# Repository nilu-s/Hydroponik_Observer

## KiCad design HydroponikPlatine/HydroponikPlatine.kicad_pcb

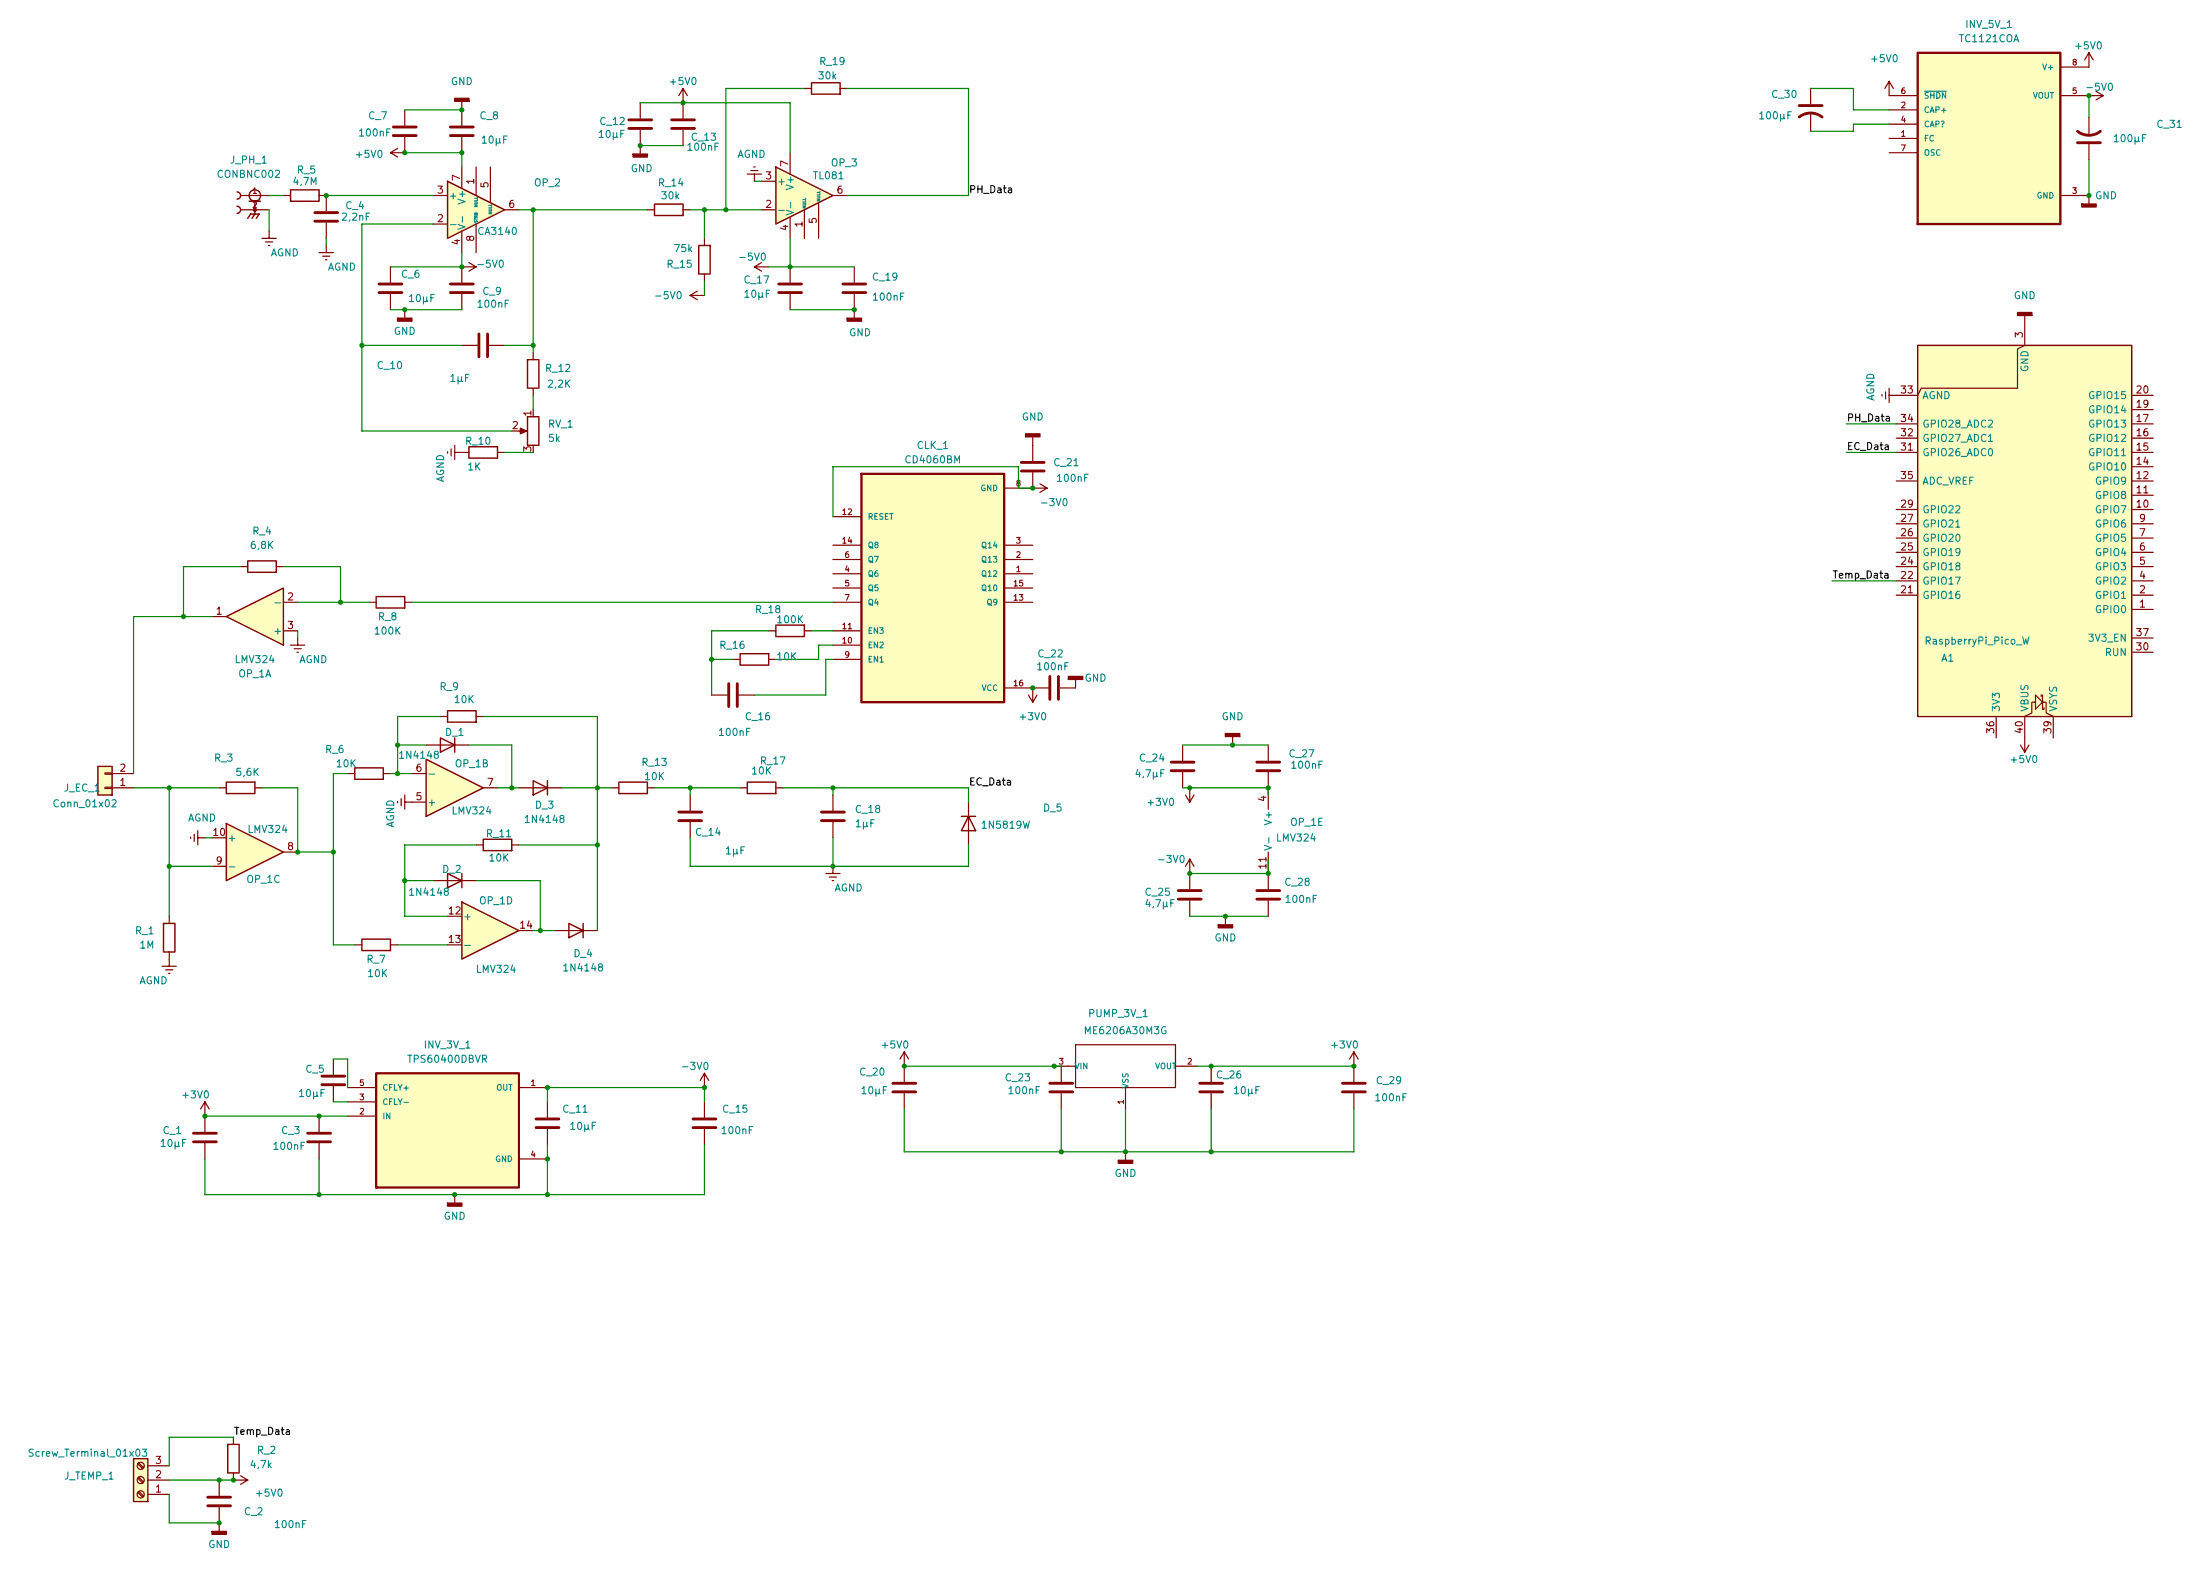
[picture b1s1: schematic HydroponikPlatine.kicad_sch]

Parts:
A1: RaspberryPi_Pico_W; RaspberryPi_Pico_Common_THT
CLK_1: CD4060BM; SOIC127P600X175-16N; LCSC C555139
C_1, C_5, C_6, C_8, C_11, C_12, C_17, C_20, C_26: 10µF; C_0201_0603Metric; LCSC C1691
C_2, C_3, C_7, C_9, C_13, C_15, C_16, C_19, C_21, C_22, C_23, C_27, C_28, C_29: 100nF; C_0402_1005Metric; LCSC C1525
C_4: 2,2nF; C_0201_0603Metric; LCSC C1531
C_10, C_14, C_18: 1µF; C_0201_0603Metric; LCSC C1592
C_24, C_25: 4,7µF; C_0201_0603Metric; LCSC C1705
C_30, C_31: 100µF; CAPPM6032X280N; LCSC C7222
D_1, D_2, D_3, D_4: 1N4148; D_SOD-123; LCSC C2099
D_5: 1N5819W; D_SOD-123F; LCSC C169540
INV_3V_1: TPS60400DBVR; SOT95P280X145-5N; LCSC C9839
INV_5V_1: TC1121COA; SOIC127P599X175-8N; LCSC C27529401
J_EC_1: Conn_01x02; JST_B2B-XH-A; LCSC C158012
J_PH_1: CONBNC002; LINX_CONBNC002; LCSC C22442694
J_TEMP_1: Screw_Terminal_01x03; TE_282834-3; LCSC C5172753
OP_1: LMV324; SOIC127P600X175-14N; LCSC C7974
OP_2: CA3140; SOIC127P602X173-8N; LCSC C5157700
OP_3: TL081; SOIC127P599X175-8N; LCSC C6965
PUMP_3V_1: ME6206A30M3G; SOT-23; MPN XC6206P332MR-G; LCSC C487911
RV_1: 5k; TRIM_3314J-1-502E; LCSC C58391
R_1: 1M; R_1206_3216Metric; LCSC C17927
R_2: 4,7k; R_0805_2012Metric; LCSC C17673
R_3: 5,6K; R_0805_2012Metric; LCSC C4382
R_4: 6,8K; R_0805_2012Metric; LCSC C17772
R_5: 4,7M; R_0402_1005Metric; LCSC C11906
R_6, R_7, R_9, R_11, R_13, R_16, R_17: 10K; R_1206_3216Metric; LCSC C1489
R_8, R_18: 100K; R_0603_1608Metric; LCSC C14675
R_10: 1K; R_1206_3216Metric; LCSC C1469
R_12: 2,2K; R_0603_1608Metric; LCSC C4190
R_14, R_19: 30k; R_0603_1608Metric; LCSC C18681
R_15: 75k; R_0805_2012Metric; LCSC C17819

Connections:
+3V0: CLK_1.16 (VCC), C_1.1, C_3.1, C_22.1, C_24.2, C_26.1, C_27.2, C_29.1, INV_3V_1.2 (IN), OP_1.4 (V+), PUMP_3V_1.2 (VOUT)
+5V0: A1.40 (VBUS), C_2.1, C_7.2, C_8.2, C_12.1, C_13.1, C_20.1, C_23.1, INV_5V_1.6 (~SHDN), INV_5V_1.8 (V+), J_TEMP_1.2, OP_2.7 (V+), OP_3.7 (V+), PUMP_3V_1.3 (VIN), R_2.1
-3V0: CLK_1.8 (GND), CLK_1.12 (RESET), C_11.1, C_15.1, C_21.1, C_25.2, C_28.2, INV_3V_1.1 (OUT), OP_1.11 (V-)
-5V0: C_6.1, C_9.1, C_17.1, C_19.1, C_31.2, INV_5V_1.5 (VOUT), OP_2.4 (V-), OP_3.4 (V-), R_15.1
/EC_Data: A1.31 (GPIO26_ADC0), C_18.1, D_5.1 (K), R_17.2
/PH_Data: A1.34 (GPIO28_ADC2), OP_3.6, R_19.2
/Temp_Data: A1.22 (GPIO17), J_TEMP_1.3, R_2.2
AGND: A1.33 (AGND), C_4.2, C_14.2, C_18.2, D_5.2 (A), J_PH_1.2, J_PH_1.S1, J_PH_1.S2, OP_1.3 (+), OP_1.5 (+), OP_1.10 (+), OP_3.3 (+), R_1.1, R_10.1
GND: A1.3 (GND), A1.8 (GND), A1.13 (GND), A1.18 (GND), A1.23 (GND), A1.28 (GND), A1.38 (GND), C_1.2, C_2.2, C_3.2, C_6.2, C_7.1, C_8.1, C_9.2, C_11.2, C_12.2, C_13.2, C_15.2, C_17.2, C_19.2, C_20.2, C_21.2, C_22.2, C_23.2, C_24.1, C_25.1, C_26.2, C_27.1, C_28.1, C_29.2, C_31.1, INV_3V_1.4 (GND), INV_5V_1.3 (GND), J_TEMP_1.1, PUMP_3V_1.1 (VSS)
unnamed: CLK_1.9 (EN1), C_16.2
unnamed: CLK_1.10 (EN2), R_16.2
unnamed: CLK_1.11 (EN3), R_18.2
unnamed: CLK_1.7 (Q4), R_8.2
unnamed: C_10.2, OP_2.6, R_12.2, R_14.1
unnamed: C_14.1, R_13.2, R_17.1
unnamed: C_16.1, R_16.1, R_18.1
unnamed: D_1.2 (A), OP_1.6 (-), R_6.2, R_9.1
unnamed: D_1.1 (K), D_3.2 (A), OP_1.7
unnamed: D_2.2 (A), OP_1.12 (+), R_11.1
unnamed: D_2.1 (K), D_4.2 (A), OP_1.14
unnamed: D_3.1 (K), D_4.1 (K), R_9.2, R_11.2, R_13.1
unnamed: C_5.1, INV_3V_1.5 (CFLY+)
unnamed: C_5.2, INV_3V_1.3 (CFLY-)
unnamed: C_30.1, INV_5V_1.2 (CAP+)
unnamed: C_30.2, INV_5V_1.4 (CAP?)
unnamed: J_EC_1.1, OP_1.9 (-), R_1.2, R_3.1
unnamed: J_EC_1.2, OP_1.1, R_4.1
unnamed: J_PH_1.1, R_5.1
unnamed: OP_1.8, R_3.2, R_6.1, R_7.1
unnamed: OP_1.2 (-), R_4.2, R_8.1
unnamed: OP_1.13 (-), R_7.2
unnamed: C_4.1, OP_2.3 (+), R_5.2
unnamed: C_10.1, OP_2.2 (-), RV_1.2
unnamed: OP_3.2 (-), R_14.2, R_15.2, R_19.1
unnamed: RV_1.1, R_12.1
unnamed: RV_1.3, R_10.2

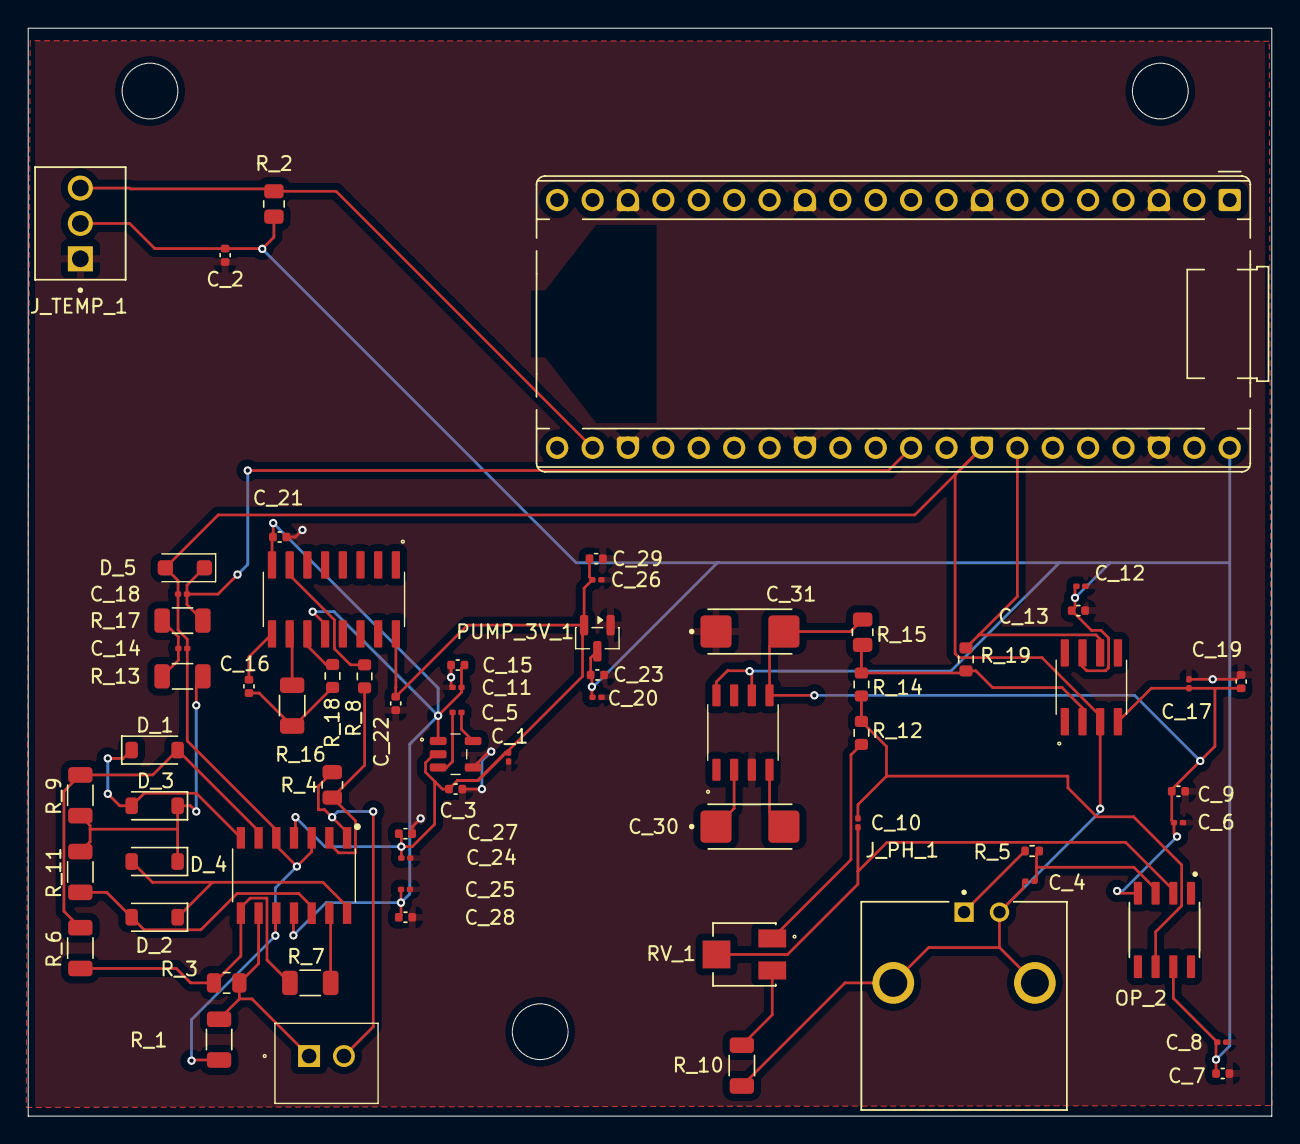
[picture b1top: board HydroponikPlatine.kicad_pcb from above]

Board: 2 copper layers, 89.2 x 78.1 mm, 67 parts (0 on the bottom side), 36 nets.

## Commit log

2026-01-23 Hydroponik Init
2026-01-23 Enhance node management and database schema. Added support for node renaming, updated node attributes (name, mode), and improved database initialization to ensure necessary columns exist. Implemented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
2026-01-26 Refactor configuration and enhance node communication. Added logging capabilities and improved serial communication with retry logic. Updated node management to support USB name handling and enhanced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
2026-01-26 Improve error handling and logging in node communication. Enhanced retry logic for serial communication and refined node discovery process. Updated node attributes for better management and ensured c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
2026-01-28 Add camera device management and update API endpoints. Introduced camera_devices module for handling camera interactions, updated API routes for camera reset and management, and refactored camera-rel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
2026-01-28 Refactor photo and readings capture logic to improve scheduling. Replaced last capture tracking with next due timestamps for better interval management. Updated frontend settings to remove references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
2026-01-28 Refactor authentication and CSRF handling in API and frontend. Updated admin reset endpoint to use environment variable for reset token. Enhanced frontend settings to manage JWT and CSRF tokens, impr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
2026-01-28 Add health check endpoint and refactor polling intervals. Introduced a new `GET /admin/health` endpoint for monitoring system status and worker metrics. Updated configuration to consolidate polling i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
2026-01-28 Refactor authentication and database handling. Disabled JWT requirement for API routes and WebSockets, simplifying access. Updated reset backend script to handle optional tokens and improved database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
2026-01-28 Update configuration documentation and refactor database reset logic. Clarified polling interval parameters in configuration files and updated data model to use minutes instead of seconds for interva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
2026-01-28 Refactor node and setup management to use `nodeId` instead of `port`. Updated API endpoints, database schema, and frontend components to reflect this change. Enhanced node identification with RP2040 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
2026-01-28 portfallbackfrontenddelete
2026-01-28 Remove outdated documentation files including API, configuration, deployment, FAQ, and troubleshooting sections. Update architecture and data model documentation to reflect current system design and 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
2026-01-28 Refactor API commands to replace `set_sim` with `set_values` for setting target values. Update documentation and frontend services accordingly to reflect this change. Adjust backend handling to ensur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
2026-01-29 Add KiCad file patterns to .gitignore and update README structure
2026-01-29 BA Structure
2026-01-30 BA Update
2026-01-30 Enhance README with updated project structure and clarify usage instructions. Streamline content for better readability and accessibility.
2026-01-30 Refactor project structure and enhance README with clearer usage instructions. Update documentation for improved readability and accessibility.
2026-01-30 BA duplica entfernt
2026-01-30 Update requirements documentation to improve clarity and structure. Refine stakeholder descriptions, enhance non-functional requirements with fit criteria, and reorganize customer and technical requi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
